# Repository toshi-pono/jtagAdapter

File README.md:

# JtagAdapter

jtag adapter using FT232H  
Created during the Security Camp 2021 X-2 track

## License

SiT2001B-MEMS-Clock-Generator symbol is based on https://github.com/asukiaaa/kicad-symbols-asukiaaa

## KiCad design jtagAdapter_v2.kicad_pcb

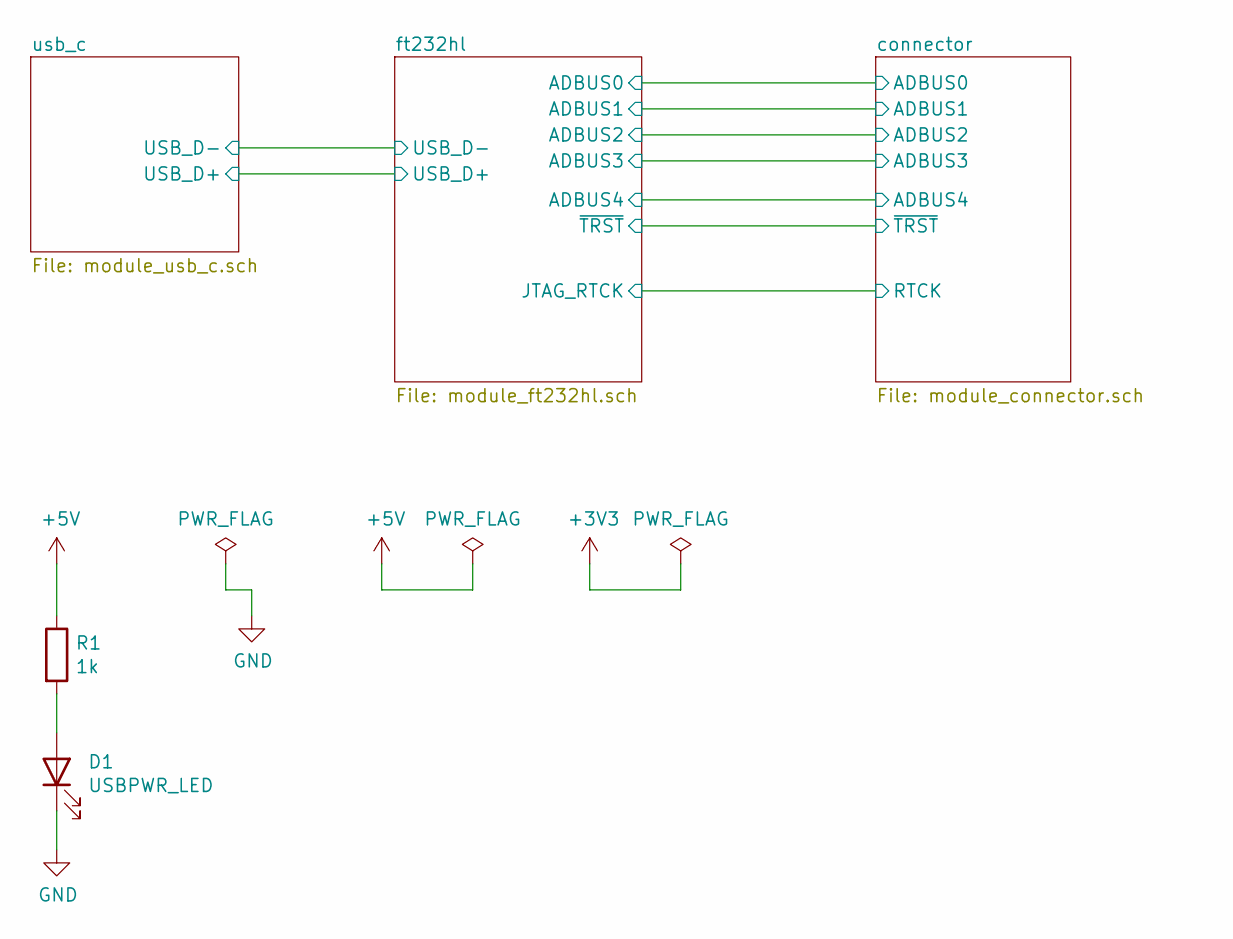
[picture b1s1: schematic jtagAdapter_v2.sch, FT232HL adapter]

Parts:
D1: USBPWR_LED; LED_0603_1608Metric_Pad1.05x0.95mm_HandSolder
R1: 1k; R_0603_1608Metric_Pad0.98x0.95mm_HandSolder

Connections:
+5V: R1.1; also elsewhere on the board
GND: D1.1 (K); also elsewhere on the board
unnamed: D1.2 (A), R1.2

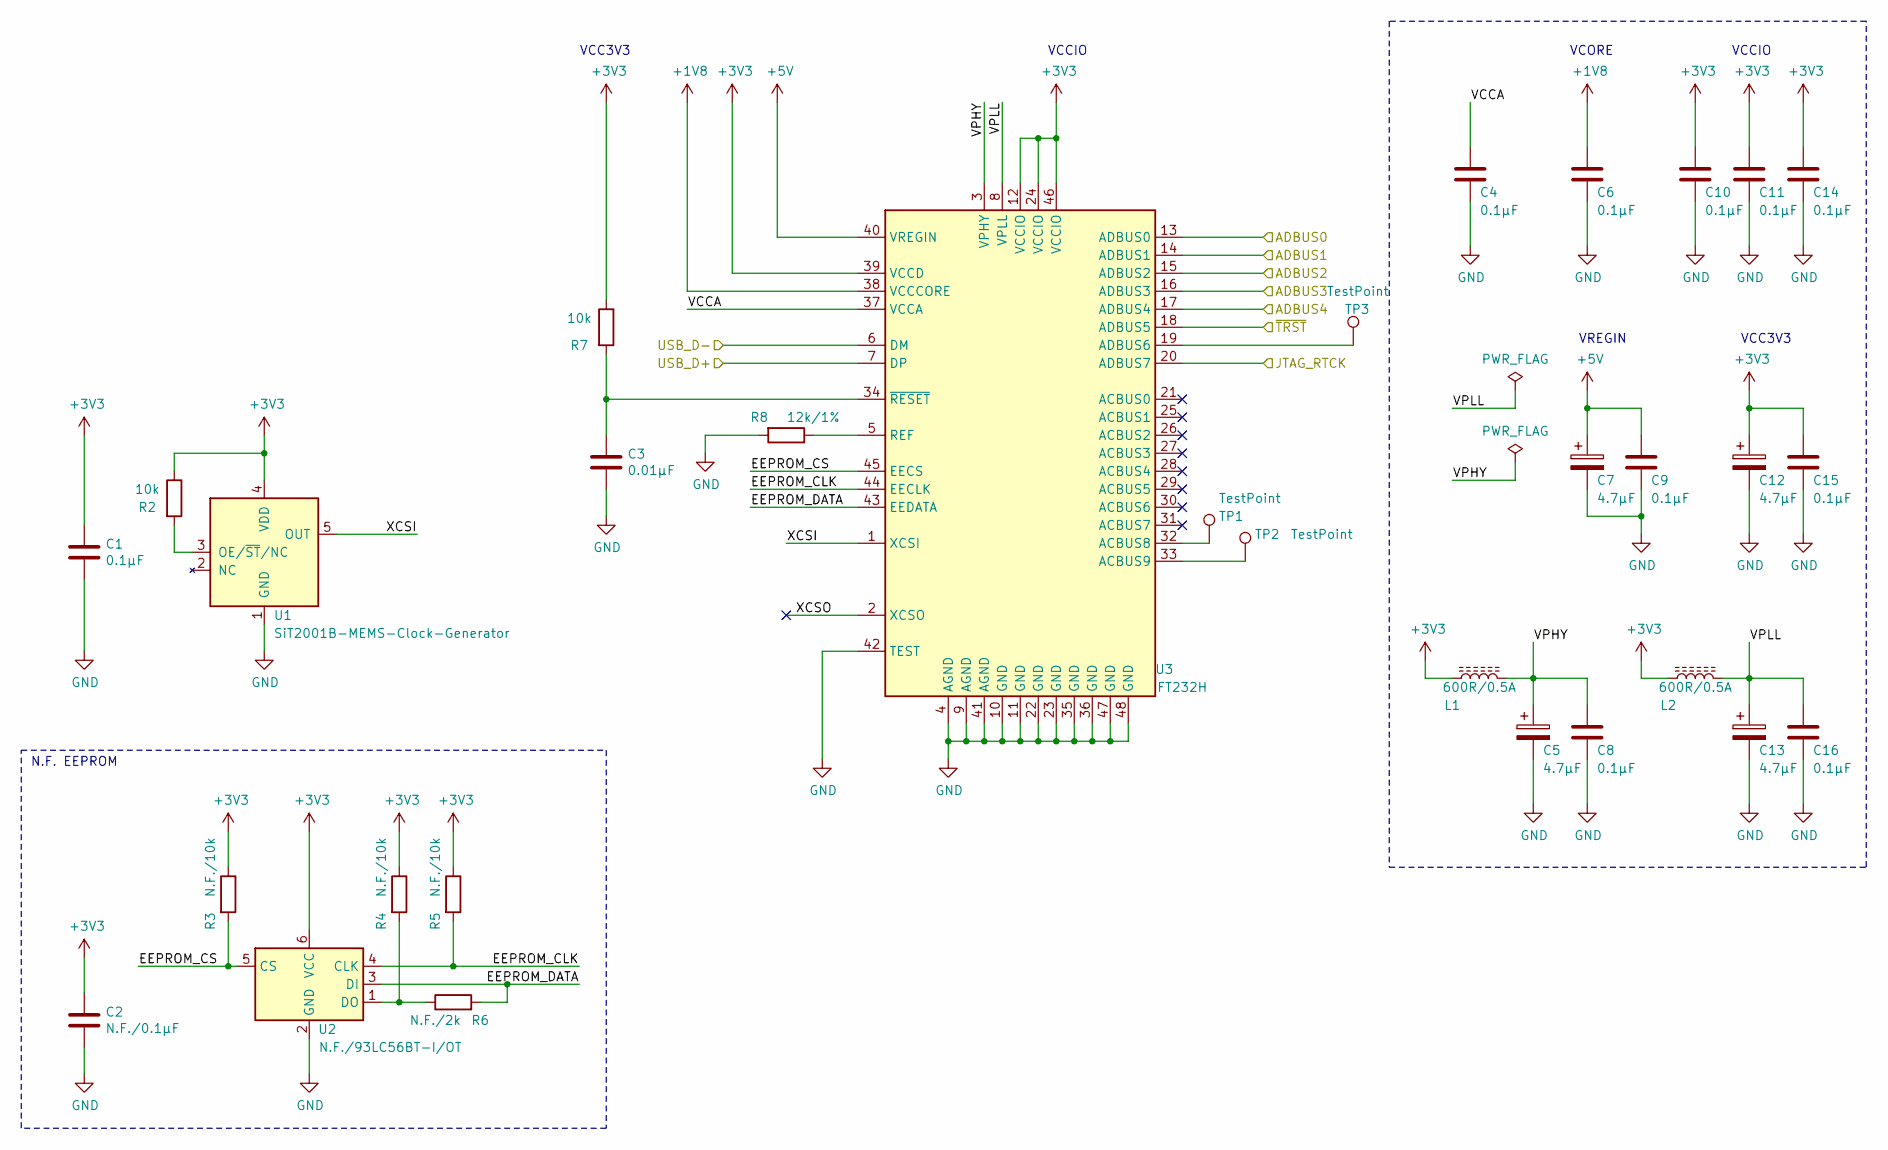
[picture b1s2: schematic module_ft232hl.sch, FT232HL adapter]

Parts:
C1, C4, C6, C8, C9, C10, C11, C14, C15, C16: 0.1μF; C_0603_1608Metric_Pad1.08x0.95mm_HandSolder
C2: N.F./0.1μF; C_0603_1608Metric_Pad1.08x0.95mm_HandSolder
C3: 0.01μF; C_0603_1608Metric_Pad1.08x0.95mm_HandSolder
C5, C7, C12, C13: 4.7μF; C_0603_1608Metric_Pad1.08x0.95mm_HandSolder
L1, L2: 600R/0.5A; L_0603_1608Metric_Pad1.05x0.95mm_HandSolder
R2, R7: 10k; R_0603_1608Metric_Pad0.98x0.95mm_HandSolder
R3, R4, R5: N.F./10k; R_0603_1608Metric_Pad0.98x0.95mm_HandSolder
R6: N.F./2k; R_0603_1608Metric_Pad0.98x0.95mm_HandSolder
R8: 12k/1%; R_0603_1608Metric_Pad0.98x0.95mm_HandSolder
TP1, TP2, TP3: TestPoint; TestPoint_Pad_D1.5mm
U1: SiT2001B-MEMS-Clock-Generator; SOT-23-5_HandSoldering
U2: N.F./93LC56BT-I/OT; SOT-23-6
U3: FT232H; LQFP-48_7x7mm_P0.5mm

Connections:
+1V8: C6.1, U3.38 (VCCCORE)
+3V3: C1.1, C2.1, C10.1, C11.1, C12.1, C14.1, C15.1, L1.1, L2.1, R2.1, R3.1, R4.1, R5.1, R7.1, U1.4 (VDD), U2.6 (VCC), U3.12 (VCCIO), U3.24 (VCCIO), U3.39 (VCCD), U3.46 (VCCIO); also elsewhere on the board
+5V: C7.1, C9.1, U3.40 (VREGIN); also elsewhere on the board
/connector/ADBUS0: U3.13 (ADBUS0); also elsewhere on the board
/connector/ADBUS1: U3.14 (ADBUS1); also elsewhere on the board
/connector/ADBUS2: U3.15 (ADBUS2); also elsewhere on the board
/connector/ADBUS3: U3.16 (ADBUS3); also elsewhere on the board
/connector/ADBUS4: U3.17 (ADBUS4); also elsewhere on the board
/connector/~TRST: U3.18 (ADBUS5); also elsewhere on the board
/ft232hl/EEPROM_CLK: R5.2, U2.4 (CLK), U3.44 (EECLK)
/ft232hl/EEPROM_CS: R3.2, U2.5 (CS), U3.45 (EECS)
/ft232hl/EEPROM_DATA: R6.2, U2.3 (DI), U3.43 (EEDATA)
/ft232hl/JTAG_RTCK: U3.20 (ADBUS7); also elsewhere on the board
/ft232hl/USB_D+: U3.7 (DP); also elsewhere on the board
/ft232hl/USB_D-: U3.6 (DM); also elsewhere on the board
/ft232hl/VCCA: C4.1, U3.37 (VCCA)
/ft232hl/VPHY: C5.1, C8.1, L1.2, U3.3 (VPHY)
/ft232hl/VPLL: C13.1, C16.1, L2.2, U3.8 (VPLL)
/ft232hl/XCSI: U1.5 (OUT), U3.1 (XCSI)
/ft232hl/XCSO: U3.2 (XCSO)
GND: C1.2, C2.2, C3.2, C4.2, C5.2, C6.2, C7.2, C8.2, C9.2, C10.2, C11.2, C12.2, C13.2, C14.2, C15.2, C16.2, R8.2, U1.1 (GND), U2.2 (GND), U3.4 (AGND), U3.9 (AGND), U3.10 (GND), U3.11 (GND), U3.22 (GND), U3.23 (GND), U3.35 (GND), U3.36 (GND), U3.41 (AGND), U3.42 (TEST), U3.47 (GND), U3.48 (GND); also elsewhere on the board
unnamed: C3.1, R7.2, U3.34 (~RESET)
unnamed: R2.2, U1.3 (OE/~ST~/NC)
unnamed: R4.2, R6.1, U2.1 (DO)
unnamed: R8.1, U3.5 (REF)
unnamed: TP1.1, U3.32 (ACBUS8)
unnamed: TP2.1, U3.33 (ACBUS9)
unnamed: TP3.1, U3.19 (ADBUS6)

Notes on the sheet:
N.F. EEPROM
VCCIO
VCORE
VCC3V3
VREGIN

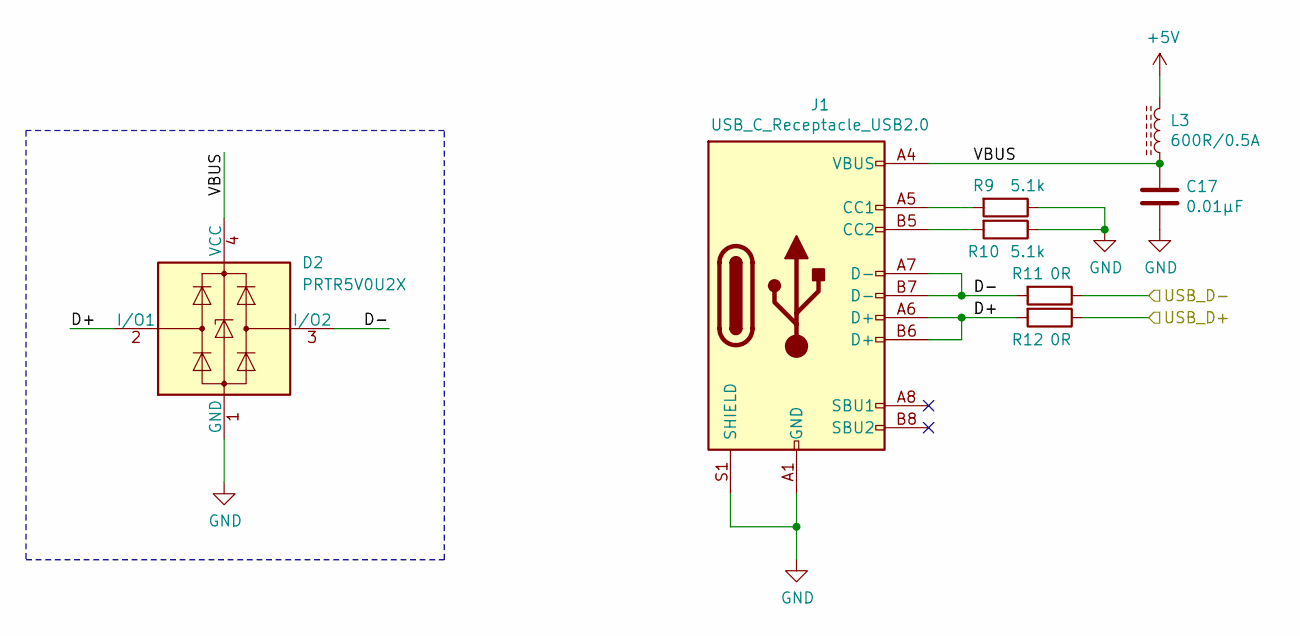
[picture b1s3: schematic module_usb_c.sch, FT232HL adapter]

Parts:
C17: 0.01μF; C_0603_1608Metric_Pad1.08x0.95mm_HandSolder
D2: PRTR5V0U2X; SOT-143
J1: USB_C_Receptacle_USB2.0; USB_C_Receptacle_GCT_USB4085
L3: 600R/0.5A; L_0603_1608Metric_Pad1.05x0.95mm_HandSolder
R9, R10: 5.1k; R_0603_1608Metric_Pad0.98x0.95mm_HandSolder
R11, R12: 0R; R_0603_1608Metric_Pad0.98x0.95mm_HandSolder

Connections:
+5V: L3.2; also elsewhere on the board
/ft232hl/USB_D+: R12.1; also elsewhere on the board
/ft232hl/USB_D-: R11.1; also elsewhere on the board
/usb_c/D+: D2.2 (I/O1), J1.A6 (D+), J1.B6 (D+), R12.2
/usb_c/D-: D2.3 (I/O2), J1.A7 (D-), J1.B7 (D-), R11.2
/usb_c/VBUS: C17.1, D2.4 (VCC), J1.A4 (VBUS), J1.A9 (VBUS), J1.B4 (VBUS), J1.B9 (VBUS), L3.1
GND: C17.2, D2.1 (GND), J1.A1 (GND), J1.A12 (GND), J1.B1 (GND), J1.B12 (GND), J1.S1 (SHIELD), R9.1, R10.1; also elsewhere on the board
unnamed: J1.A5 (CC1), R9.2
unnamed: J1.B5 (CC2), R10.2

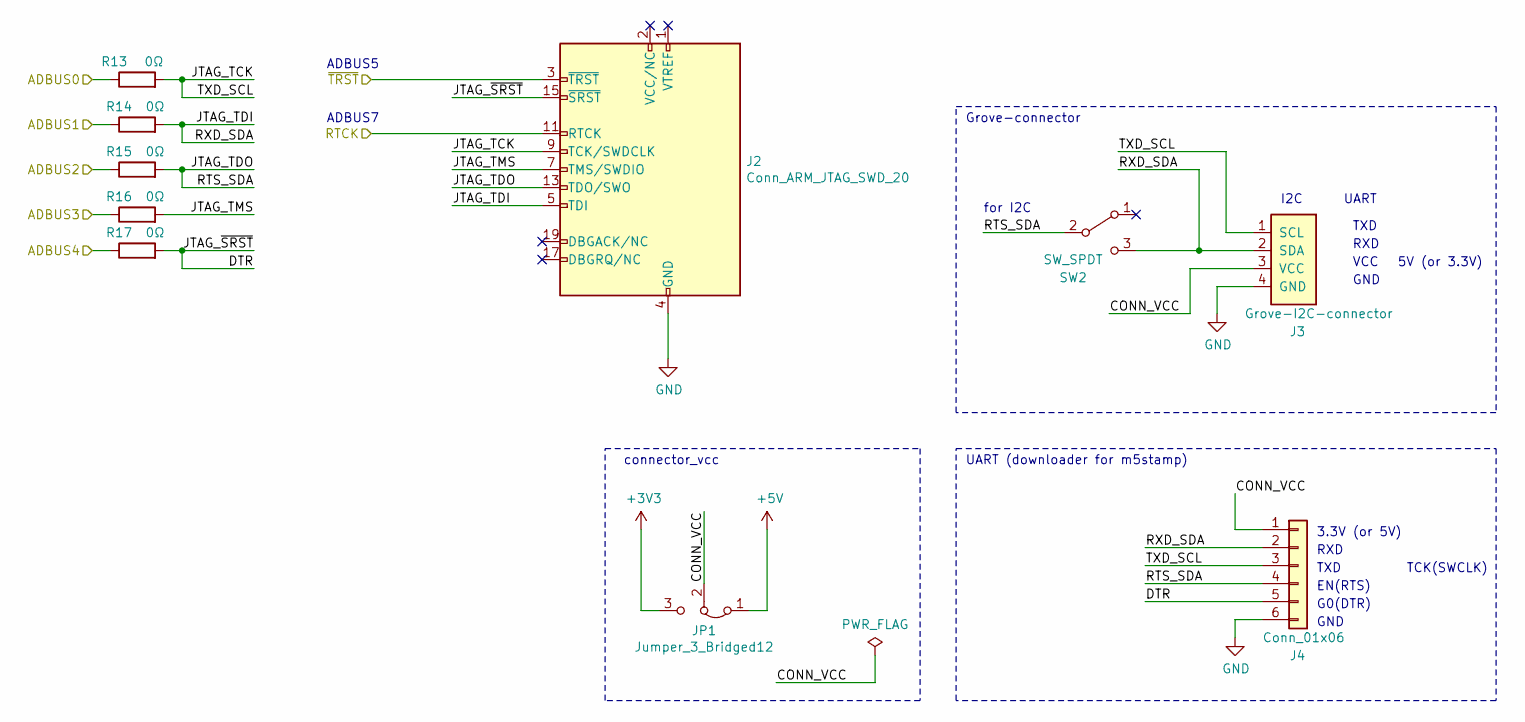
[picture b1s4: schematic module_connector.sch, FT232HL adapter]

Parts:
J2: Conn_ARM_JTAG_SWD_20; PinHeader_2x10_P2.54mm_Horizontal
J3: Grove-I2C-connector; NS-Tech_Grove_1x04_P2mm_Vertical
J4: Conn_01x06; PinHeader_1x06_P2.54mm_Vertical
JP1: Jumper_3_Bridged12; PinHeader_1x03_P2.54mm_Vertical
R13, R14, R15, R16, R17: 0Ω; R_0603_1608Metric_Pad0.98x0.95mm_HandSolder
SW2: SW_SPDT; PinHeader_1x03_P2.54mm_Vertical

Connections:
+3V3: JP1.3 (B); also elsewhere on the board
+5V: JP1.1 (A); also elsewhere on the board
/connector/ADBUS0: R13.1; also elsewhere on the board
/connector/ADBUS1: R14.1; also elsewhere on the board
/connector/ADBUS2: R15.1; also elsewhere on the board
/connector/ADBUS3: R16.1; also elsewhere on the board
/connector/ADBUS4: R17.1; also elsewhere on the board
/connector/CONN_VCC: J3.3 (VCC), J4.1, JP1.2 (C)
/connector/DTR: J2.15 (~SRST~), J4.5, R17.2
/connector/JTAG_TCK: J2.9 (TCK/SWDCLK), J3.1 (SCL), J4.3, R13.2
/connector/JTAG_TDI: J2.5 (TDI), J3.2 (SDA), J4.2, R14.2, SW2.3 (C)
/connector/JTAG_TDO: J2.13 (TDO/SWO), J4.4, R15.2, SW2.2 (B)
/connector/JTAG_TMS: J2.7 (TMS/SWDIO), R16.2
/connector/~TRST: J2.3 (~TRST~); also elsewhere on the board
/ft232hl/JTAG_RTCK: J2.11 (RTCK); also elsewhere on the board
GND: J2.4 (GND), J2.6 (GND), J2.8 (GND), J2.10 (GND), J2.12 (GND), J2.14 (GND), J2.16 (GND), J2.18 (GND), J2.20 (GND), J3.4 (GND), J4.6; also elsewhere on the board

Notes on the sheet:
I2C
UART
TXD
RXD
VCC
GND
Grove-connector
3.3V (or 5V)
EN(RTS)
G0(DTR)
UART (downloader for m5stamp)
connector_vcc
5V (or 3.3V)
for I2C
ADBUS5
ADBUS7
TCK(SWCLK)

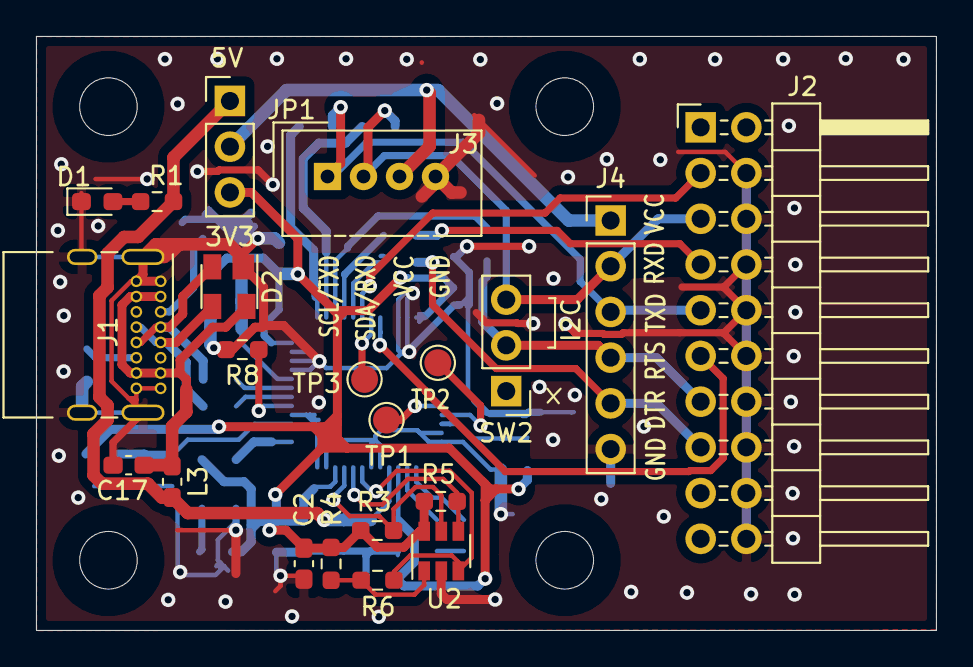
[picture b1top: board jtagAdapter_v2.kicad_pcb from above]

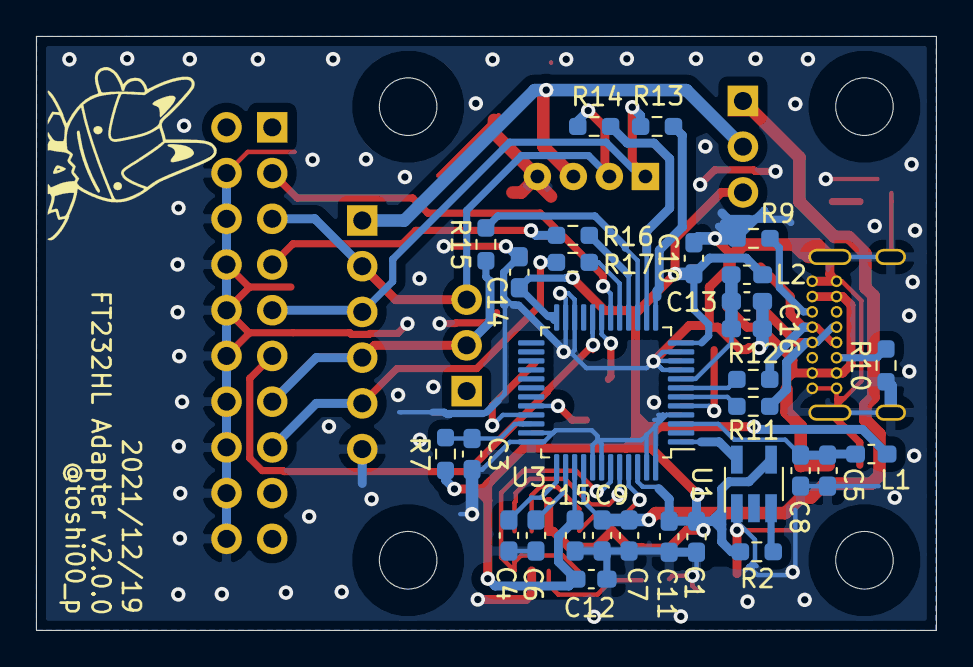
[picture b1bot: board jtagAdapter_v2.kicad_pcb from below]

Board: 2 copper layers, 50.0 x 33.0 mm, 51 parts (30 on the bottom side), 39 nets.

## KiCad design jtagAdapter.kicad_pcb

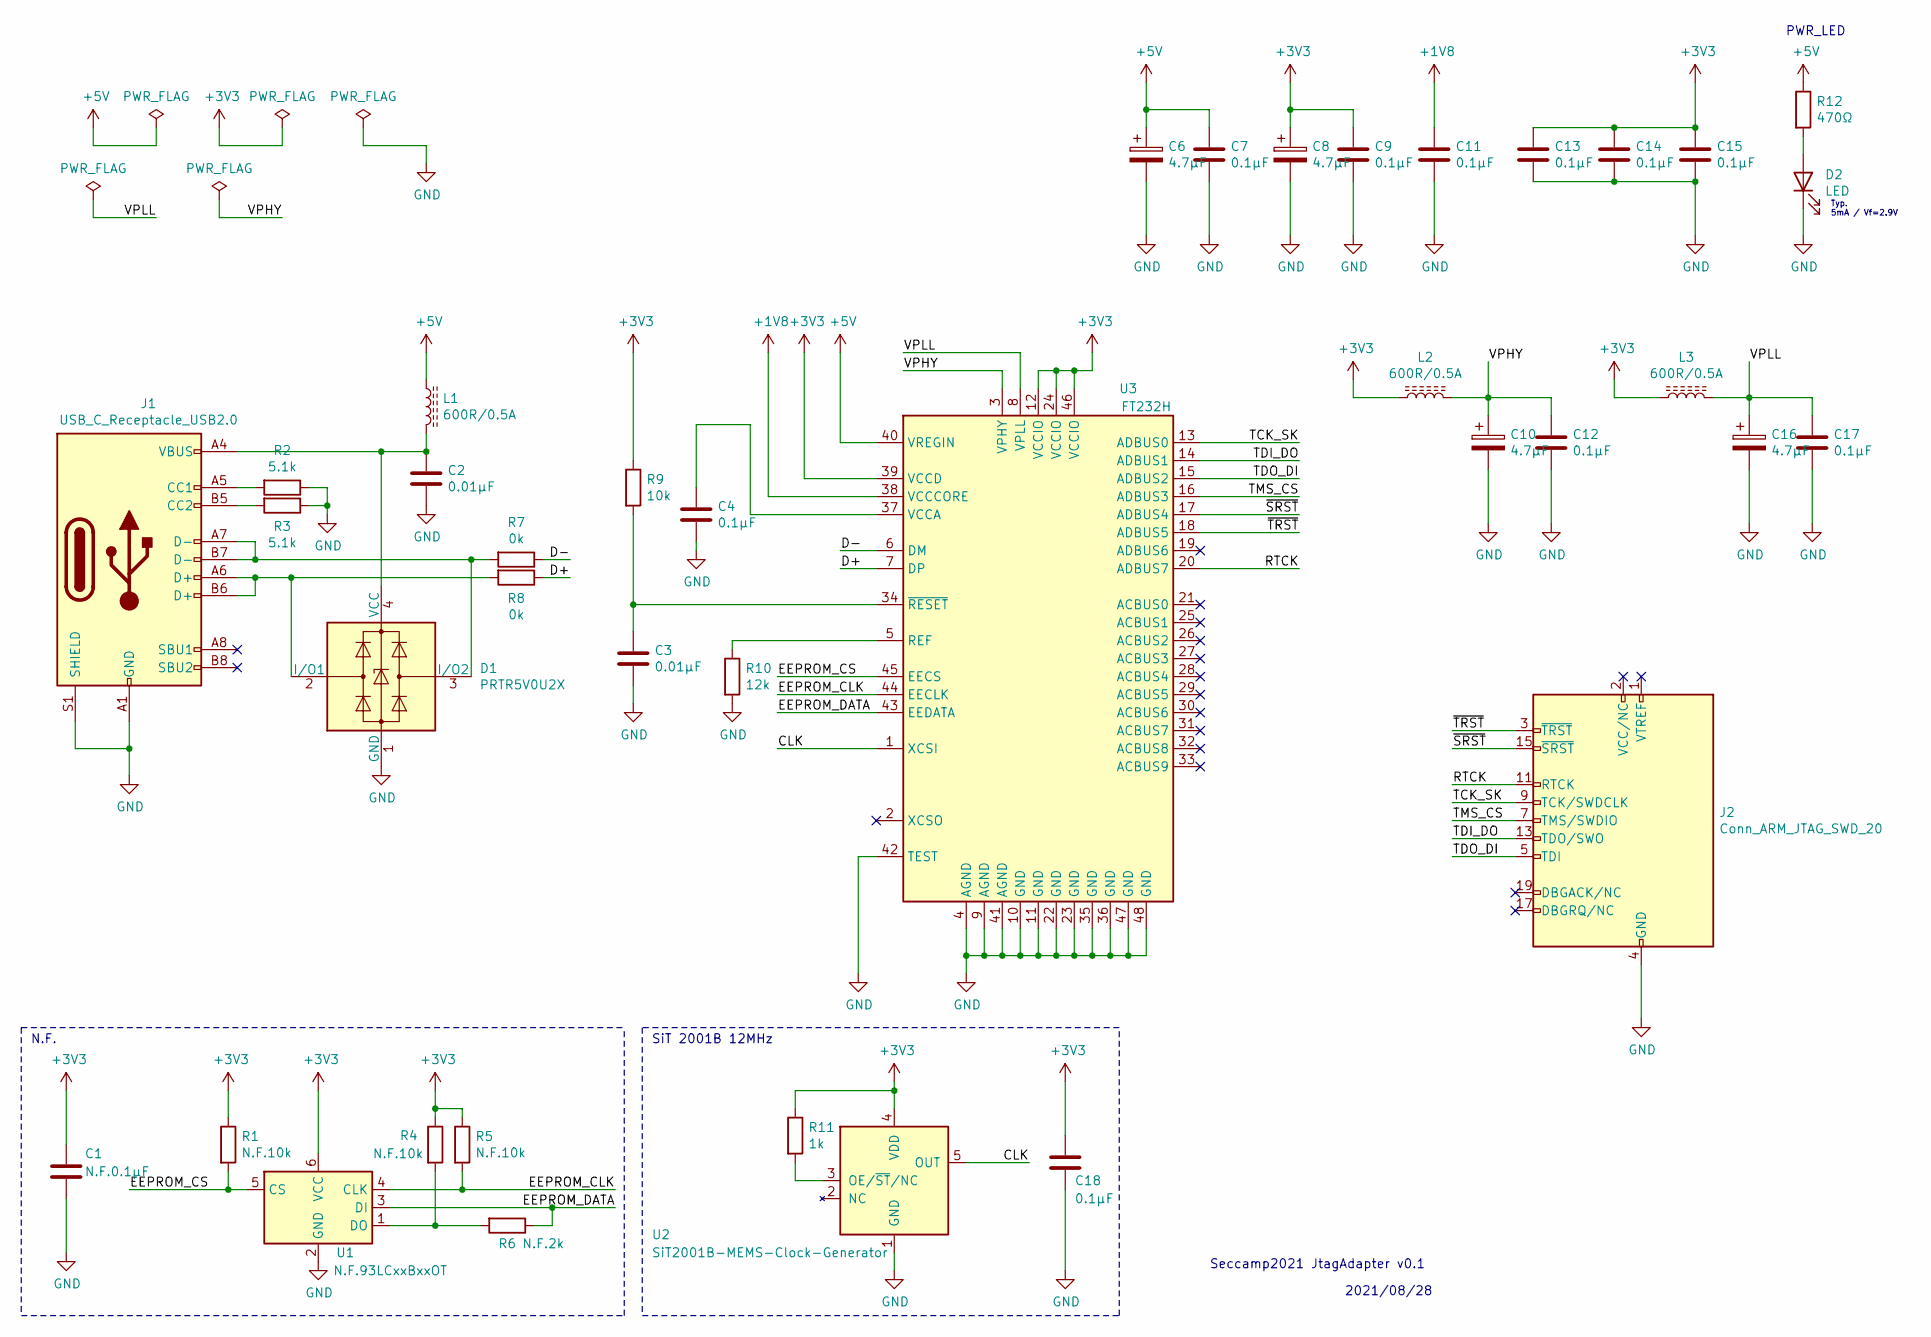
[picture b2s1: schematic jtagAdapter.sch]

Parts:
C1: N.F.0.1μF; C_0603_1608Metric_Pad1.08x0.95mm_HandSolder
C2, C3: 0.01μF; C_0603_1608Metric_Pad1.08x0.95mm_HandSolder
C4, C7, C9, C11, C12, C13, C14, C15, C17, C18: 0.1μF; C_0603_1608Metric_Pad1.08x0.95mm_HandSolder
C6, C8, C10, C16: 4.7μF; C_0603_1608Metric_Pad1.08x0.95mm_HandSolder
D1: PRTR5V0U2X; SOT-143
D2: LED; LED_0603_1608Metric_Castellated
J1: USB_C_Receptacle_USB2.0; USB_C_Receptacle_GCT_USB4085
J2: Conn_ARM_JTAG_SWD_20; IDC-Header_2x10_P2.54mm_Vertical
L1, L2, L3: 600R/0.5A; L_0603_1608Metric_Pad1.05x0.95mm_HandSolder
R1, R4, R5: N.F.10k; R_0603_1608Metric_Pad0.98x0.95mm_HandSolder
R2, R3: 5.1k; R_0603_1608Metric_Pad0.98x0.95mm_HandSolder
R6: N.F.2k; R_0603_1608Metric_Pad0.98x0.95mm_HandSolder
R7, R8: 0k; R_0603_1608Metric_Pad0.98x0.95mm_HandSolder
R9: 10k; R_0603_1608Metric_Pad0.98x0.95mm_HandSolder
R10: 12k; R_0603_1608Metric_Pad0.98x0.95mm_HandSolder
R11: 1k; R_0603_1608Metric_Pad0.98x0.95mm_HandSolder
R12: 470Ω; R_0603_1608Metric_Pad0.98x0.95mm_HandSolder
U1: N.F.93LCxxBxxOT; SOT-23-6
U2: SiT2001B-MEMS-Clock-Generator; SOT-23-5_HandSoldering
U3: FT232H; LQFP-48_7x7mm_P0.5mm

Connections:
+1V8: C11.1, U3.38 (VCCCORE)
+3V3: C1.1, C8.1, C9.1, C13.1, C14.1, C15.1, C18.1, L2.1, L3.1, R1.1, R4.1, R5.1, R9.1, R11.1, U1.6 (VCC), U2.4 (VDD), U3.12 (VCCIO), U3.24 (VCCIO), U3.39 (VCCD), U3.46 (VCCIO)
+5V: C6.1, C7.1, L1.1, R12.1, U3.40 (VREGIN)
/CLK: U2.5 (OUT), U3.1 (XCSI)
/D+: R8.1, U3.7 (DP)
/D-: R7.1, U3.6 (DM)
/EEPROM_CLK: R5.2, U1.4 (CLK), U3.44 (EECLK)
/EEPROM_CS: R1.2, U1.5 (CS), U3.45 (EECS)
/EEPROM_DATA: R6.1, U1.3 (DI), U3.43 (EEDATA)
/RTCK: J2.11 (RTCK), U3.20 (ADBUS7)
/TCK_SK: J2.9 (TCK/SWDCLK), U3.13 (ADBUS0)
/TDI_DO: J2.13 (TDO/SWO), U3.14 (ADBUS1)
/TDO_DI: J2.5 (TDI), U3.15 (ADBUS2)
/TMS_CS: J2.7 (TMS/SWDIO), U3.16 (ADBUS3)
/VPHY: C10.1, C12.1, L2.2, U3.3 (VPHY)
/VPLL: C16.1, C17.1, L3.2, U3.8 (VPLL)
/~SRST: J2.15 (~SRST~), U3.17 (ADBUS4)
/~TRST: J2.3 (~TRST~), U3.18 (ADBUS5)
GND: C1.2, C2.2, C3.2, C4.1, C6.2, C7.2, C8.2, C9.2, C10.2, C11.2, C12.2, C13.2, C14.2, C15.2, C16.2, C17.2, C18.2, D1.1 (GND), D2.1 (K), J1.A1 (GND), J1.A12 (GND), J1.B1 (GND), J1.B12 (GND), J1.S1 (SHIELD), J2.4 (GND), J2.6 (GND), J2.8 (GND), J2.10 (GND), J2.12 (GND), J2.14 (GND), J2.16 (GND), J2.18 (GND), J2.20 (GND), R2.1, R3.1, R10.2, U1.2 (GND), U2.1 (GND), U3.4 (AGND), U3.9 (AGND), U3.10 (GND), U3.11 (GND), U3.22 (GND), U3.23 (GND), U3.35 (GND), U3.36 (GND), U3.41 (AGND), U3.42 (TEST), U3.47 (GND), U3.48 (GND)
unnamed: C2.1, D1.4 (VCC), J1.A4 (VBUS), J1.A9 (VBUS), J1.B4 (VBUS), J1.B9 (VBUS), L1.2
unnamed: C3.1, R9.2, U3.34 (~RESET)
unnamed: C4.2, U3.37 (VCCA)
unnamed: D1.2 (I/O1), J1.A6 (D+), J1.B6 (D+), R8.2
unnamed: D1.3 (I/O2), J1.A7 (D-), J1.B7 (D-), R7.2
unnamed: D2.2 (A), R12.2
unnamed: J1.A5 (CC1), R2.2
unnamed: J1.B5 (CC2), R3.2
unnamed: R4.2, R6.2, U1.1 (DO)
unnamed: R10.1, U3.5 (REF)
unnamed: R11.2, U2.3 (OE/~ST~/NC)

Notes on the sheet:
N.F.
PWR_LED
Seccamp2021 JtagAdapter v0.1
2021/08/28
SiT 2001B 12MHz
Typ. 5mA / Vf=2.9V

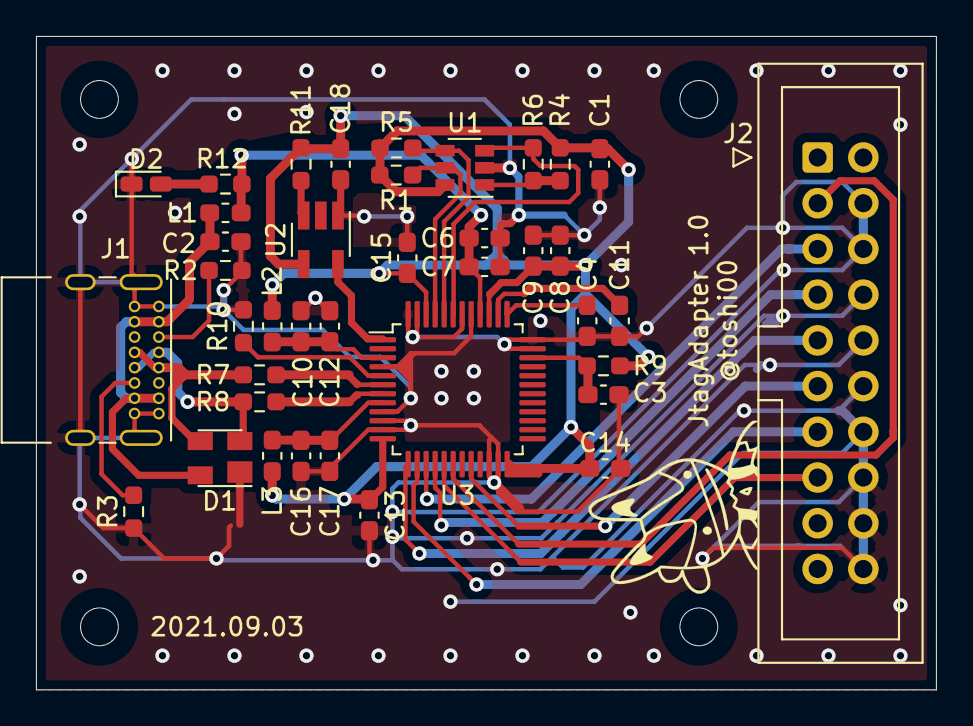
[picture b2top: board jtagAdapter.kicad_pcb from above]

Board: 2 copper layers, 50.0 x 36.3 mm, 43 parts (0 on the bottom side), 30 nets.

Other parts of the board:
 : MountingHole_2.1mm
 #2,  #3,  #4: MountingHole_2.1mm

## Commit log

2021-09-13 init
2021-09-13 remove unnecessary files
2021-12-20 .netファイルを削除
2021-12-20 v2.0.0を作成
2021-12-20 画像を追加
2021-12-20 サイズ調整
2021-12-20 画像を添付
2021-12-31 USB-Cフットプリントのエラーを修正
